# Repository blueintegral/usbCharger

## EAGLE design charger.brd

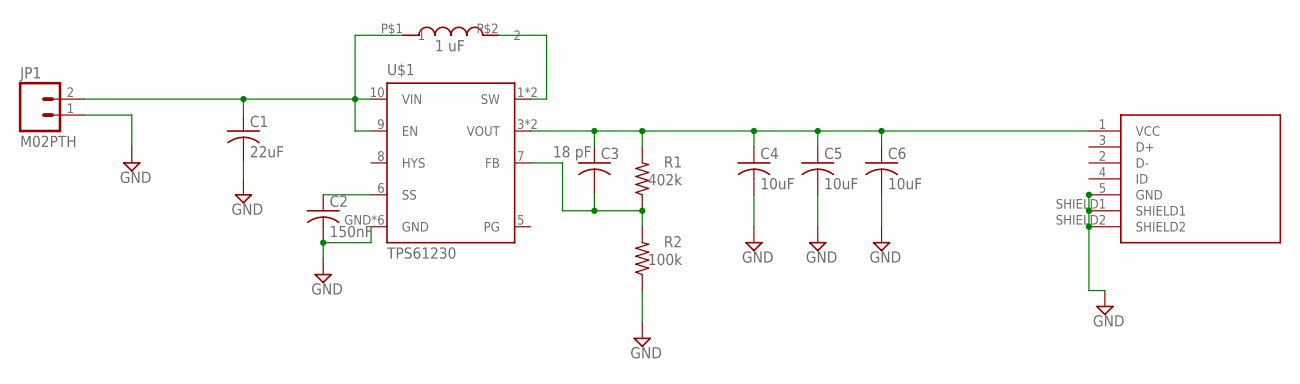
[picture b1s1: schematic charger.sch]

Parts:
C1: 22uF; C1206
C2: 150nF; C0603K
C3: 18 pF; C0603K
C4, C5, C6: 10uF; C0805K
JP1: M02PTH; 1X02
R1: 402k; R0603
R2: 100k; R0603
U$1: TPS61230; DRC-S-PVSON-N11
U$3: SRU1028
U$4: USB2

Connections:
GND: C1.2, C2.2, C4.2, C5.2, C6.2, JP1.1, R2.1, U$1.GND, U$1.GND@1 (GND), U$1.GND@2 (GND), U$1.GND@3 (GND), U$1.GND@4 (GND), U$1.GND@5 (GND), U$4.5 (GND), U$4.SHIELD1, U$4.SHIELD2
IND: U$1.1 (SW), U$1.2 (SW), U$3.P$2 (2)
unnamed: C2.1, U$1.6 (SS)
unnamed: C3.2, R1.1, R2.2, U$1.7 (FB)
PG: U$1.5 (PG)
VIN: C1.1, JP1.2, U$1.9 (EN), U$1.10 (VIN), U$3.P$1 (1)
VOUT: C3.1, C4.1, C5.1, C6.1, R1.2, U$1.3 (VOUT), U$1.4 (VOUT), U$4.1 (VCC)

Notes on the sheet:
1 uF

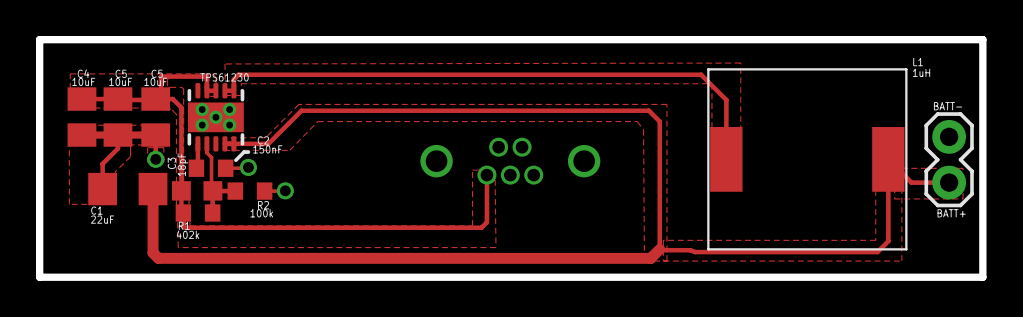
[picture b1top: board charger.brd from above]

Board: 2 copper layers, 52.4 x 13.2 mm, 12 parts (0 on the bottom side), 6 nets.

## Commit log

2014-07-19 :octocat: Added .gitattributes & .gitignore files
2014-07-20 First version of schematic and layout
2014-07-22 Fixed inductor footprint, updated layout
2014-07-25 Added a smaller version without weird USB connector
2014-08-14 Fixed dimensions and updated USB connector
2014-08-15 Centered connector, changed length back to 52mm

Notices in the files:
parts and their libraries:
SparkFun-Connectors: Licensing: Creative Commons ShareAlike 4.0 International - https://creativecommons.org/licenses/by-sa/4.0
